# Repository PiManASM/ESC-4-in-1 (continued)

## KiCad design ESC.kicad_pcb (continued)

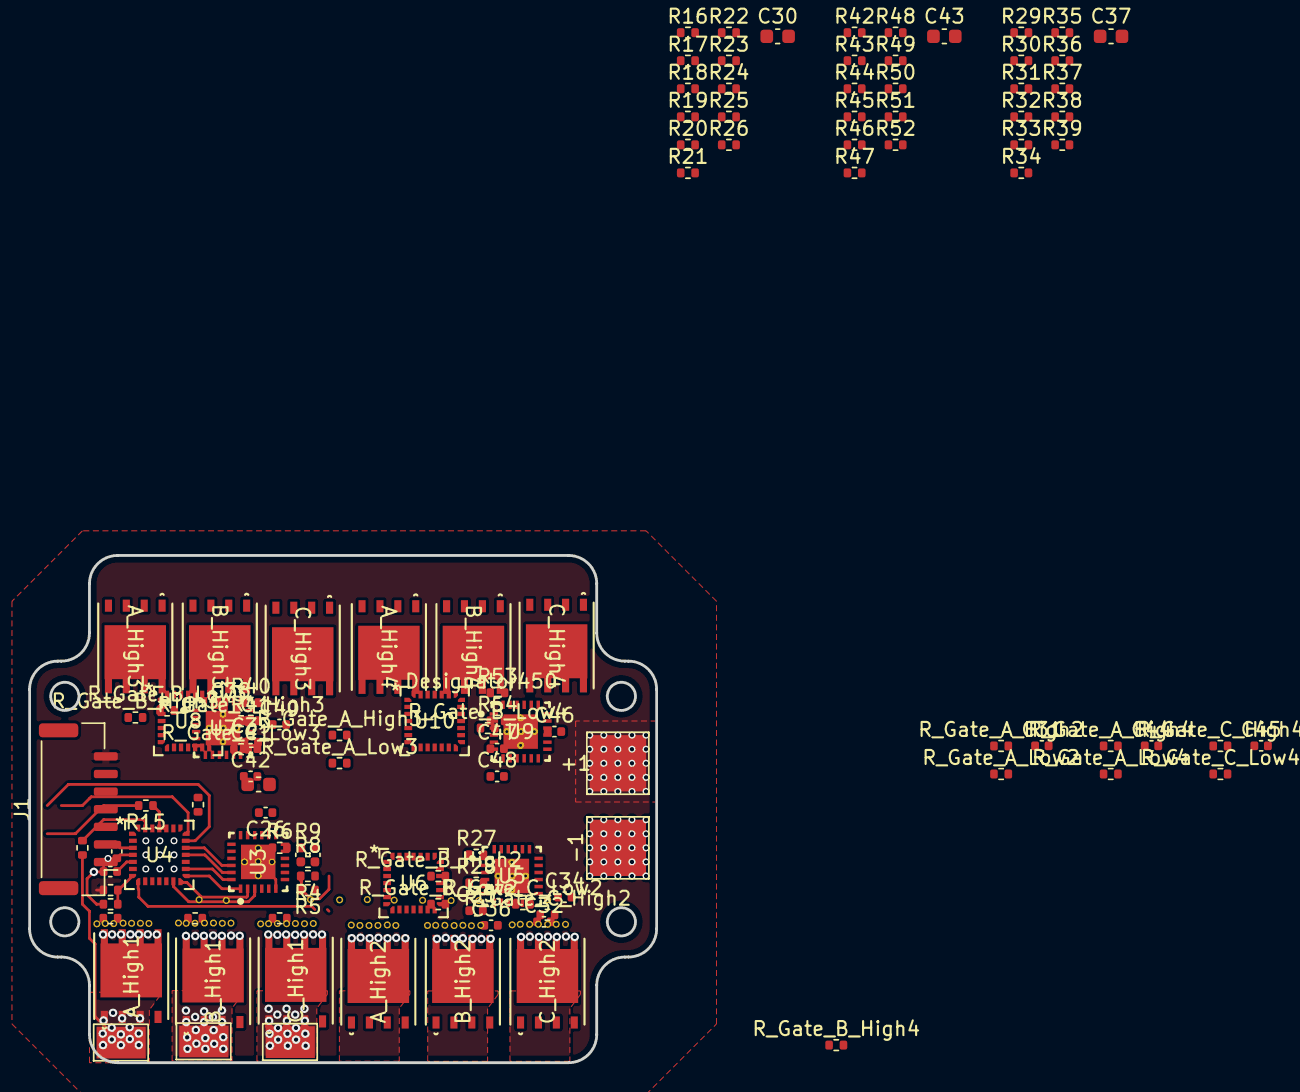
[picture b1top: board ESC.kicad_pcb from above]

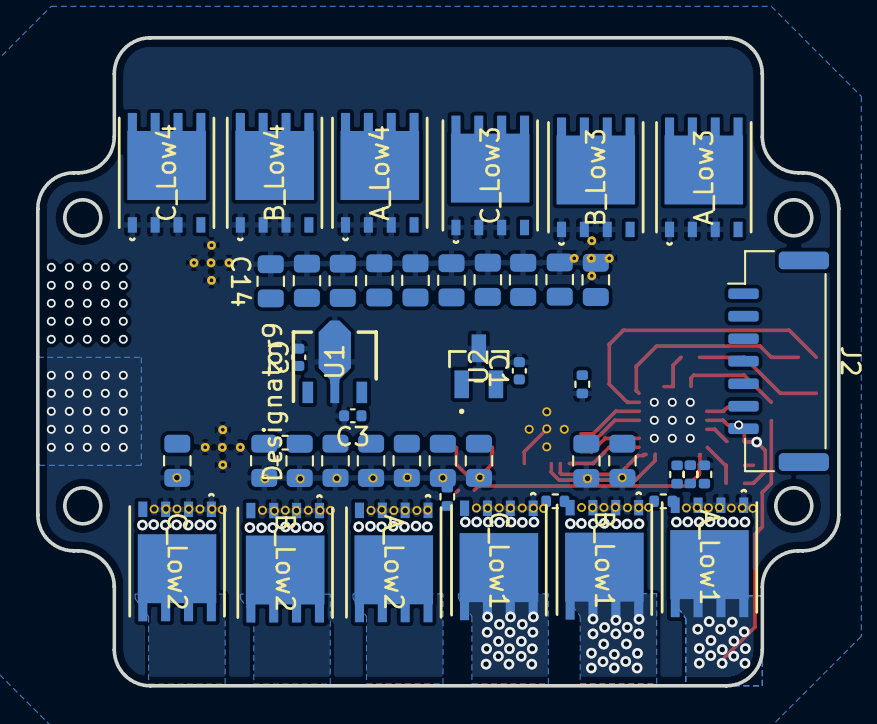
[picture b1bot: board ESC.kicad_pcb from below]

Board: 8 copper layers, 44.5 x 36.0 mm, 166 parts (46 on the bottom side), 141 nets.

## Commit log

2025-02-07 Transfer from other repo
    Initial commit to Github
2025-02-07 Fixed pin names
    reset pins to apply proper net names
2025-02-08 added additional layers and planes
2025-02-10 more routing
2025-03-31 more routing and placement
